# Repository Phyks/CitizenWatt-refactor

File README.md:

CitizenWatt-refactor
====================

This is an updated version of [CitizenWatt](http://citizenwatt.paris/) code,
aiming to be a backup of available stuff, with minor updates for anyone
willing to build its own.

CitizenWatt aimed at building a personal DIY energy consumption meter,
inspired by [OpenEnergyMonitor](https://openenergymonitor.org/).

I recently came across cloned CitizenWatt repositories and wanted to make some
lifting of the code, while I set it back in place at home. I also found out
that OpenEnergyMonitor was considerably nicer than it used to be, especially
from a UX point of view. This aims at being an up to date merge of
OpenEnergyMonitor and CitizenWatt, to be the best combination possible at the
moment, in my opinion.

This is part of a home automation process, hence the will to avoid installing
pre-compiled images which are not easily extensible.

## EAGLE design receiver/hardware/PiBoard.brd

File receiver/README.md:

CitizenWatt-PiBoard
===================

The small piece of PCB to connect the NRF24L01+ to the Pi

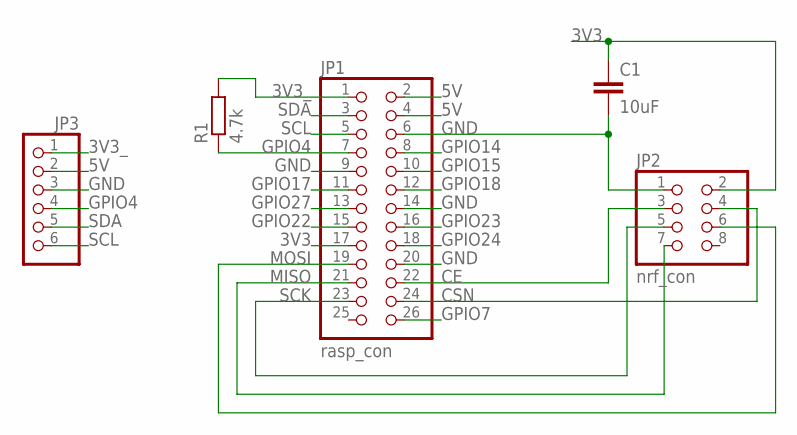
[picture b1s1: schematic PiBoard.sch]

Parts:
C1: 10uF; 1206
JP1: rasp_con; 2X13
JP2: nrf_con; 2X04
JP3: PINHD-1X6; 1X06
R1: 4.7k; R1206

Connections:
3V3: C1.1, JP1.17, JP2.2
3V3_: JP1.1, JP3.1, R1.2
5V: JP1.2, JP1.4, JP3.2
CE: JP1.22, JP2.3
CSN: JP1.24, JP2.4
GND: C1.2, JP1.6, JP1.9, JP1.14, JP1.20, JP2.1, JP3.3
GPIO4: JP1.7, JP3.4, R1.1
GPIO7: JP1.26
GPIO14: JP1.8
GPIO15: JP1.10
GPIO17: JP1.11
GPIO18: JP1.12
GPIO22: JP1.15
GPIO23: JP1.16
GPIO24: JP1.18
GPIO27: JP1.13
MISO: JP1.21, JP2.7
MOSI: JP1.19, JP2.6
SCK: JP1.23, JP2.5
SCL: JP1.5, JP3.6
SDA: JP1.3, JP3.5

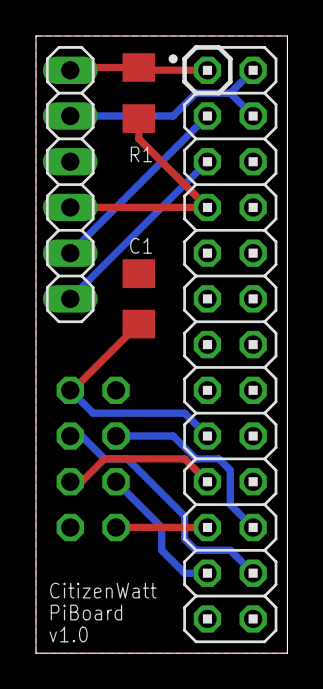
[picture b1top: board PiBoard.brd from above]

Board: 2 copper layers, 14.0 x 34.3 mm, 5 parts (1 on the bottom side), 12 nets.

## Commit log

2017-02-27 Add README.md
2017-02-27 Reimport projects into this one
2017-02-27 Move stuff around

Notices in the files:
parts and their libraries:
SparkFun-Capacitors: Licensing: CC v3.0 Share-Alike You are welcome to use this library for commercial purposes.
